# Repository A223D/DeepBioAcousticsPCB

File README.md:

# DeepBioAcousticsPCB
PCB for the Capstone Project Deep Bio Acoustics

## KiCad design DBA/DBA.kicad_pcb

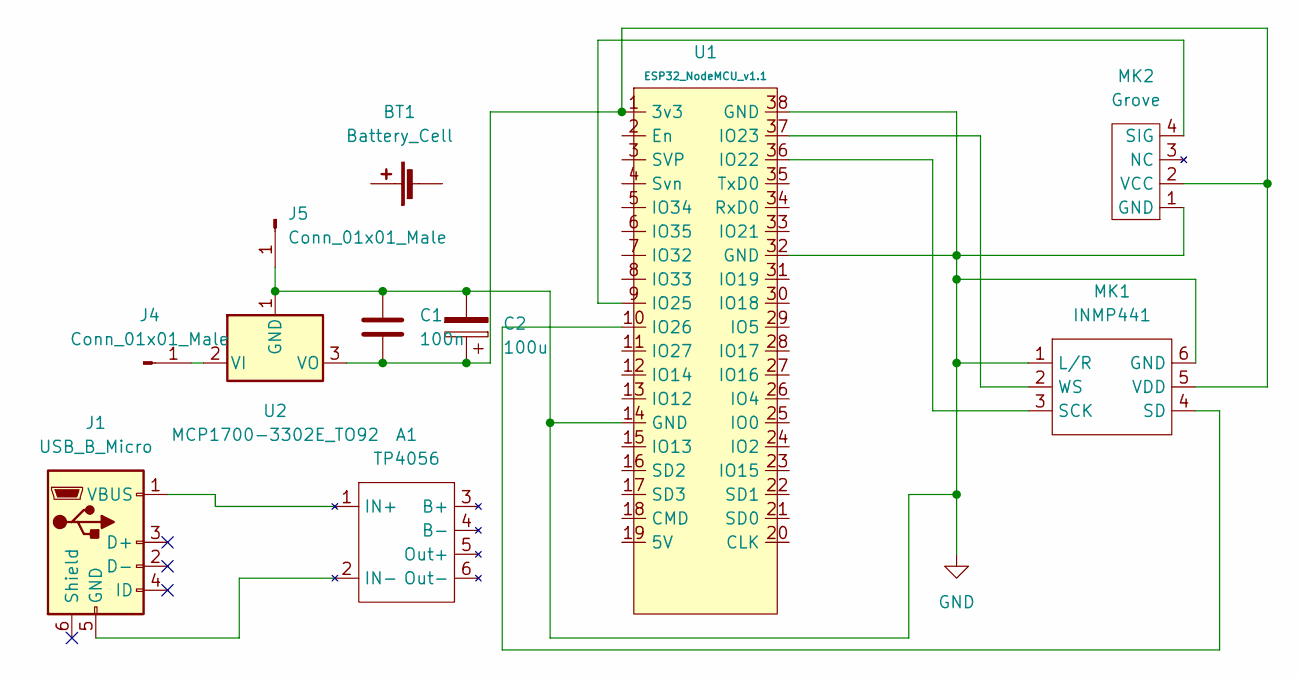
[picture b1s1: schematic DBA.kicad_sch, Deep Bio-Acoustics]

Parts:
A1: TP4056; TP4056Board
BT1: Battery_Cell; Battery_Custom
C1: 100n; C_Radial_D6.3mm_H5.0mm_P2.50mm
C2: 100u; CP_Radial_D5.0mm_P2.50mm
J1: USB_B_Micro
J4, J5: Conn_01x01_Male; PinHeader_1x01_P2.54mm_Vertical
MK1: INMP441
MK2: Grove; Grove Sound Sensor
U1: ESP32_NodeMCU_v1.1; DIP-38_W22.86mm
U2: MCP1700-3302E_TO92; TO-92_Inline

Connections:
GND: C1.1, C2.2, J5.1, MK1.1 (L/R), MK1.6 (GND), MK2.1 (GND), U1.14 (GND), U1.32 (GND), U1.38 (GND), U2.1 (GND)
unnamed: C1.2, C2.1, MK1.5 (VDD), MK2.2 (VCC), U1.1 (3v3), U2.3 (VO)
unnamed: A1.1 (IN+), J1.1 (VBUS)
unnamed: A1.2 (IN-), J1.5 (GND)
unnamed: J4.1, U2.2 (VI)
unnamed: MK1.2 (WS), U1.37 (IO23)
unnamed: MK1.3 (SCK), U1.36 (IO22)
unnamed: MK1.4 (SD), U1.10 (IO26)
unnamed: MK2.4 (SIG), U1.9 (IO25)

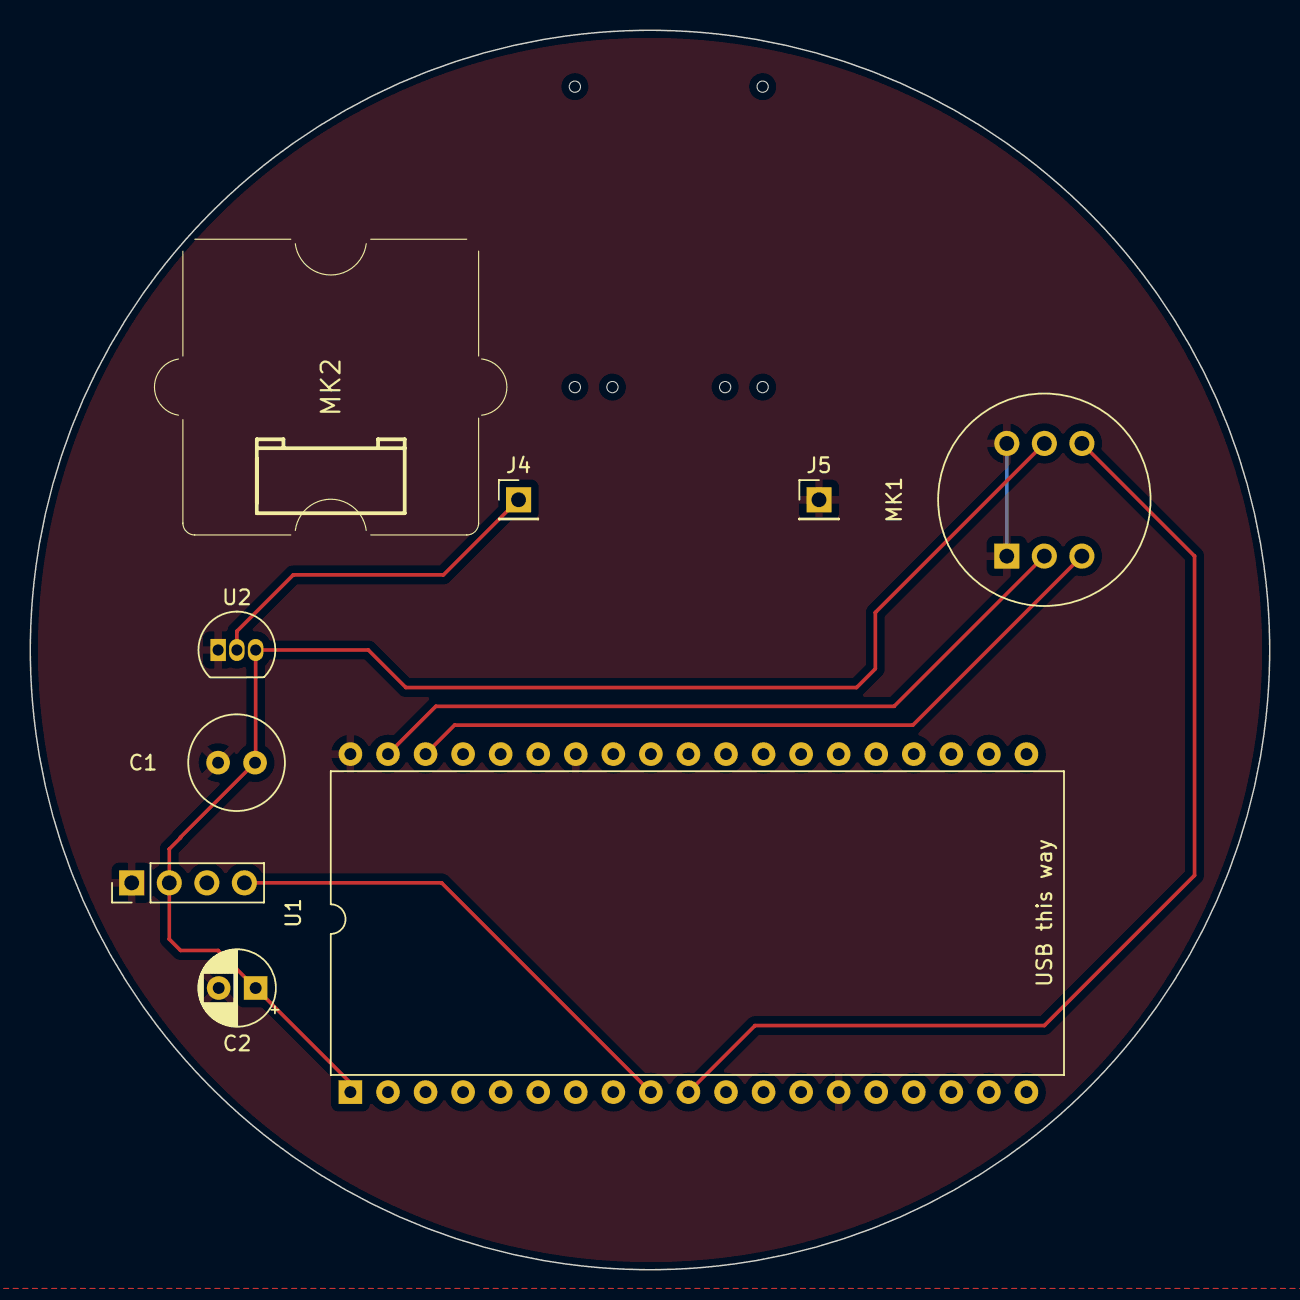
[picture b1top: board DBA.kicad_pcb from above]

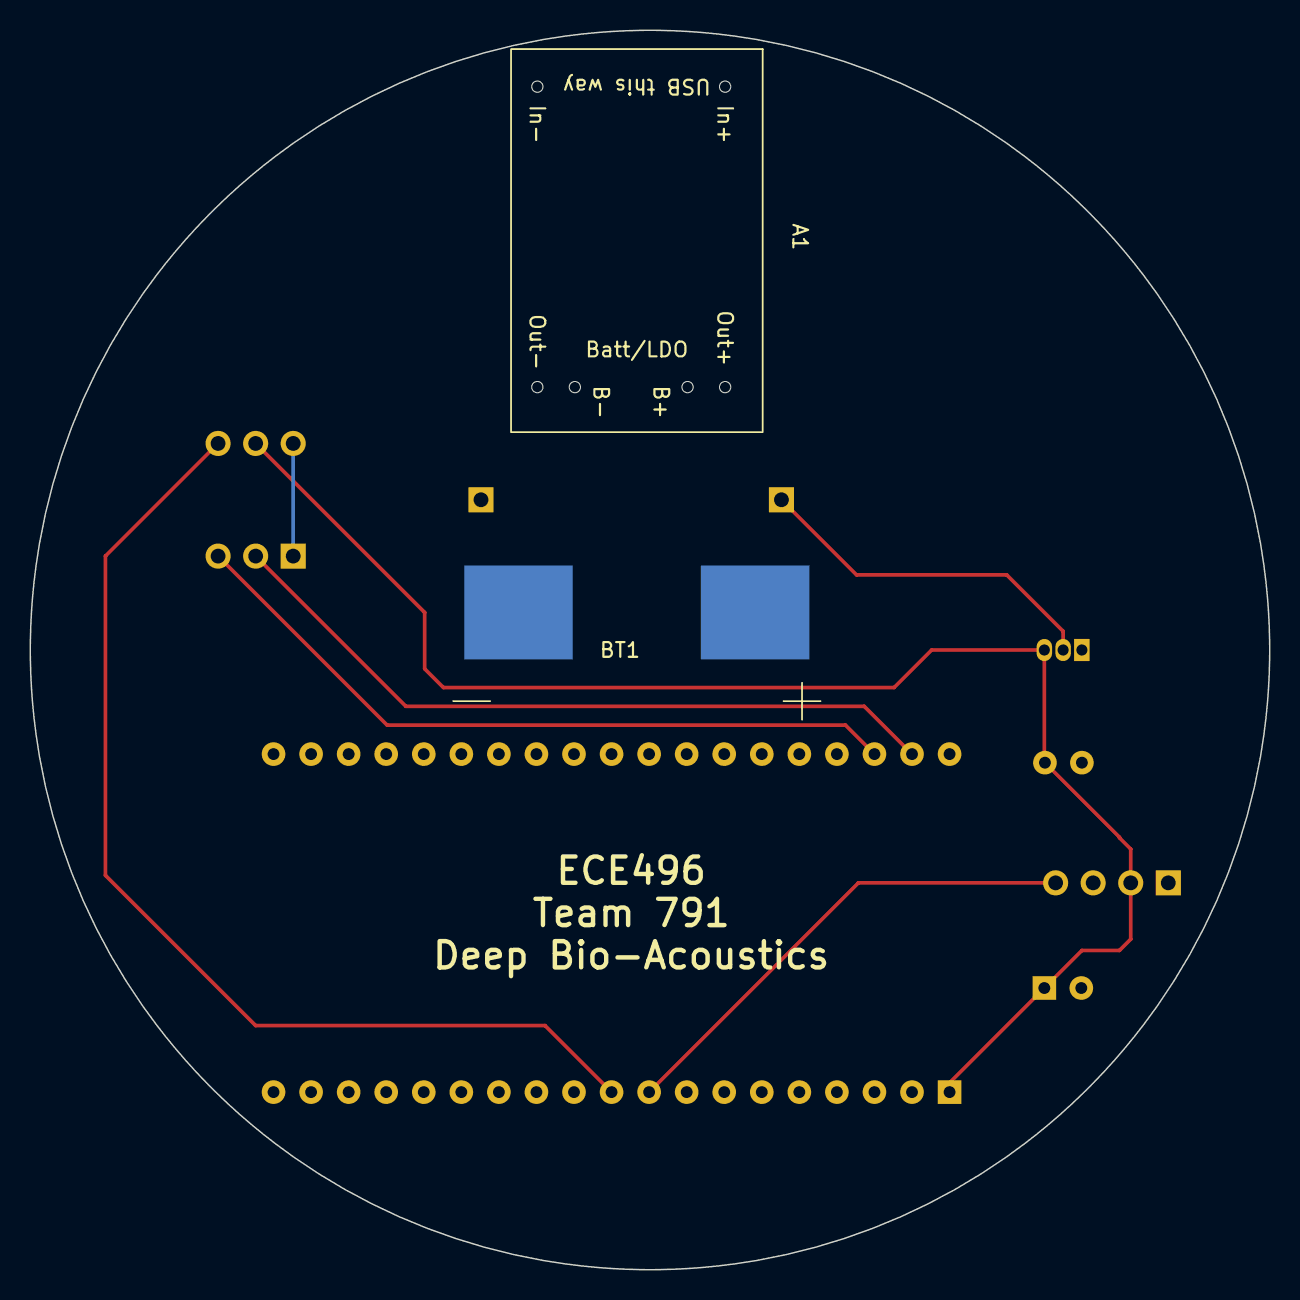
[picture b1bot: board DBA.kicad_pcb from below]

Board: 2 copper layers, 83.8 x 83.8 mm, 10 parts (2 on the bottom side), 7 nets.

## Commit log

2024-01-18 Changed README to test github push
2024-01-19 Created symbol for ESP32 NodeMCU
2024-01-19 Created symbols for primary and secondary microphone
2024-01-20 First complete model
2024-02-27 Did some shit idk. This is the new first complete model
2024-02-27 first circular version{
2024-02-27 Final circular design
2024-03-12 Added gerber files
2024-03-12 Added key for transfer
